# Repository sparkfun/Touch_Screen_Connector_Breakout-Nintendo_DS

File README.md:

SparkFun Touch Screen Connector Breakout - Nintendo DS
========================================

[*SparkFun Touch Screen Connector Breakout - Nintendo DS (BOB-09170)*](https://www.sparkfun.com/products/9170)

This a breakout board for the SMD connector for the Nintendo DS touch screen. 
4-pin right angle ZIF connector at 0.5 mm pitch broken out to 4 0.1 inch spaced headers.

Repository Contents
-------------------

* **/Hardware** - Eagle design files (.brd, .sch)
* **/Production** - Production panel files (.brd)

Documentation
--------------

* **[SparkFun Fritzing repo](https://github.com/sparkfun/Fritzing_Parts)** - Fritzing diagrams for SparkFun products.
* **[SparkFun 3D Model repo](https://github.com/sparkfun/3D_Models)** - 3D models of SparkFun products. 

License Information
-------------------
This product is _**open source**_! 

The **hardware** is released under [Creative Commons ShareAlike 4.0 International](https://creativecommons.org/licenses/by-sa/4.0/).

Please use, reuse, and modify these files as you see fit. Please maintain attribution to SparkFun Electronics and release anything derivative under the same license.

Distributed as-is; no warranty is given.

- Your friends at SparkFun.

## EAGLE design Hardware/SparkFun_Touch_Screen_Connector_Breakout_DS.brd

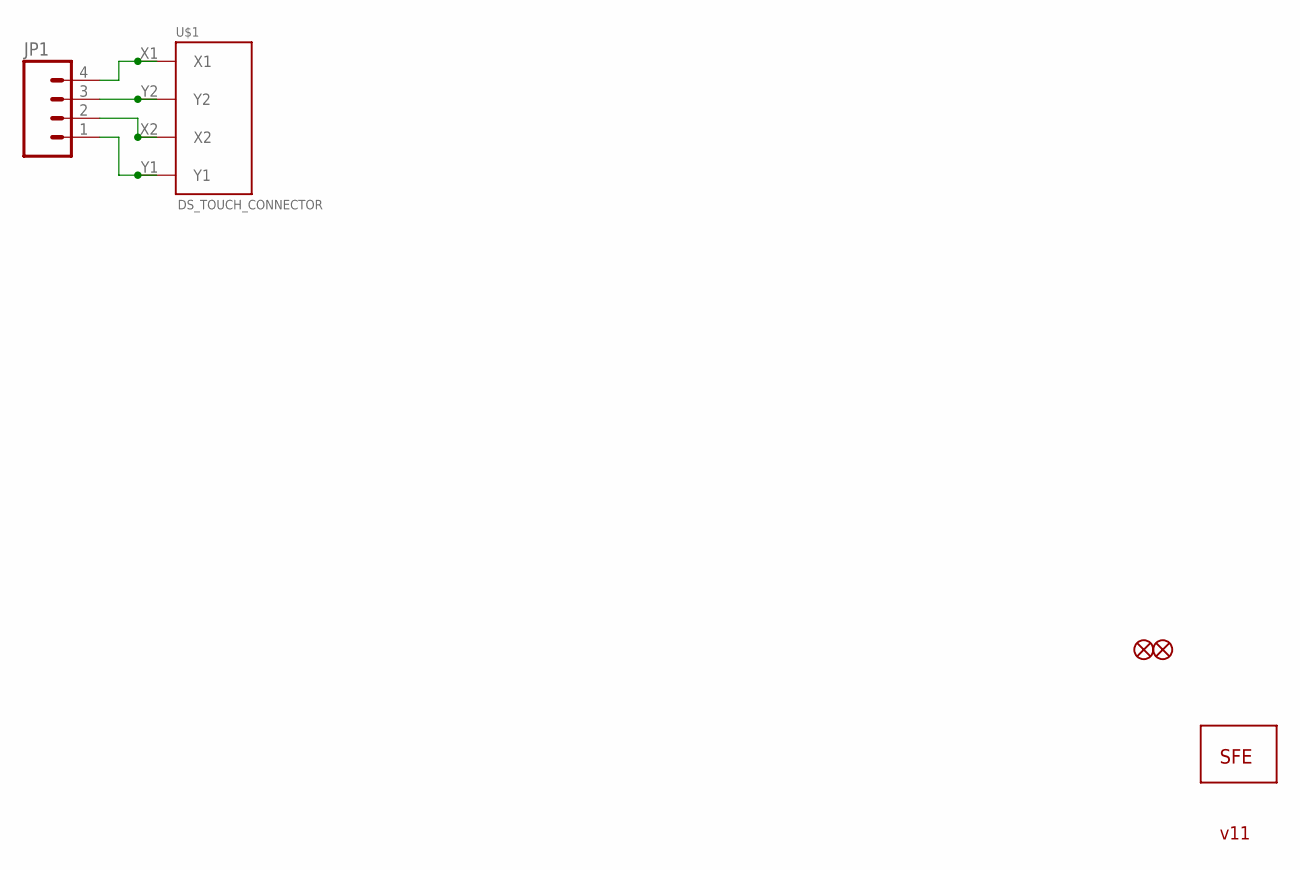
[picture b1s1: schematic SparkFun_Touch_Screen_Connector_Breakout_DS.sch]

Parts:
FID1, FID2: FIDUCIAL1X2; FIDUCIAL-1X2
JP1: M04PTH; 1X04
U$1: DS_TOUCH_CONNECTOR
U$2: LOGO-SFESK; SFE-LOGO-FLAME

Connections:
unnamed: JP1.4, U$1.X1
unnamed: JP1.3, U$1.Y2
unnamed: JP1.2, U$1.X2
unnamed: JP1.1, U$1.Y1

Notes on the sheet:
v11

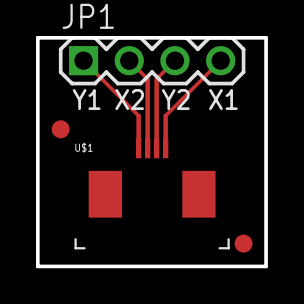
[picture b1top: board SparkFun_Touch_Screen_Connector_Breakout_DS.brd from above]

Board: 2 copper layers, 12.7 x 12.7 mm, 5 parts (1 on the bottom side), 4 nets.

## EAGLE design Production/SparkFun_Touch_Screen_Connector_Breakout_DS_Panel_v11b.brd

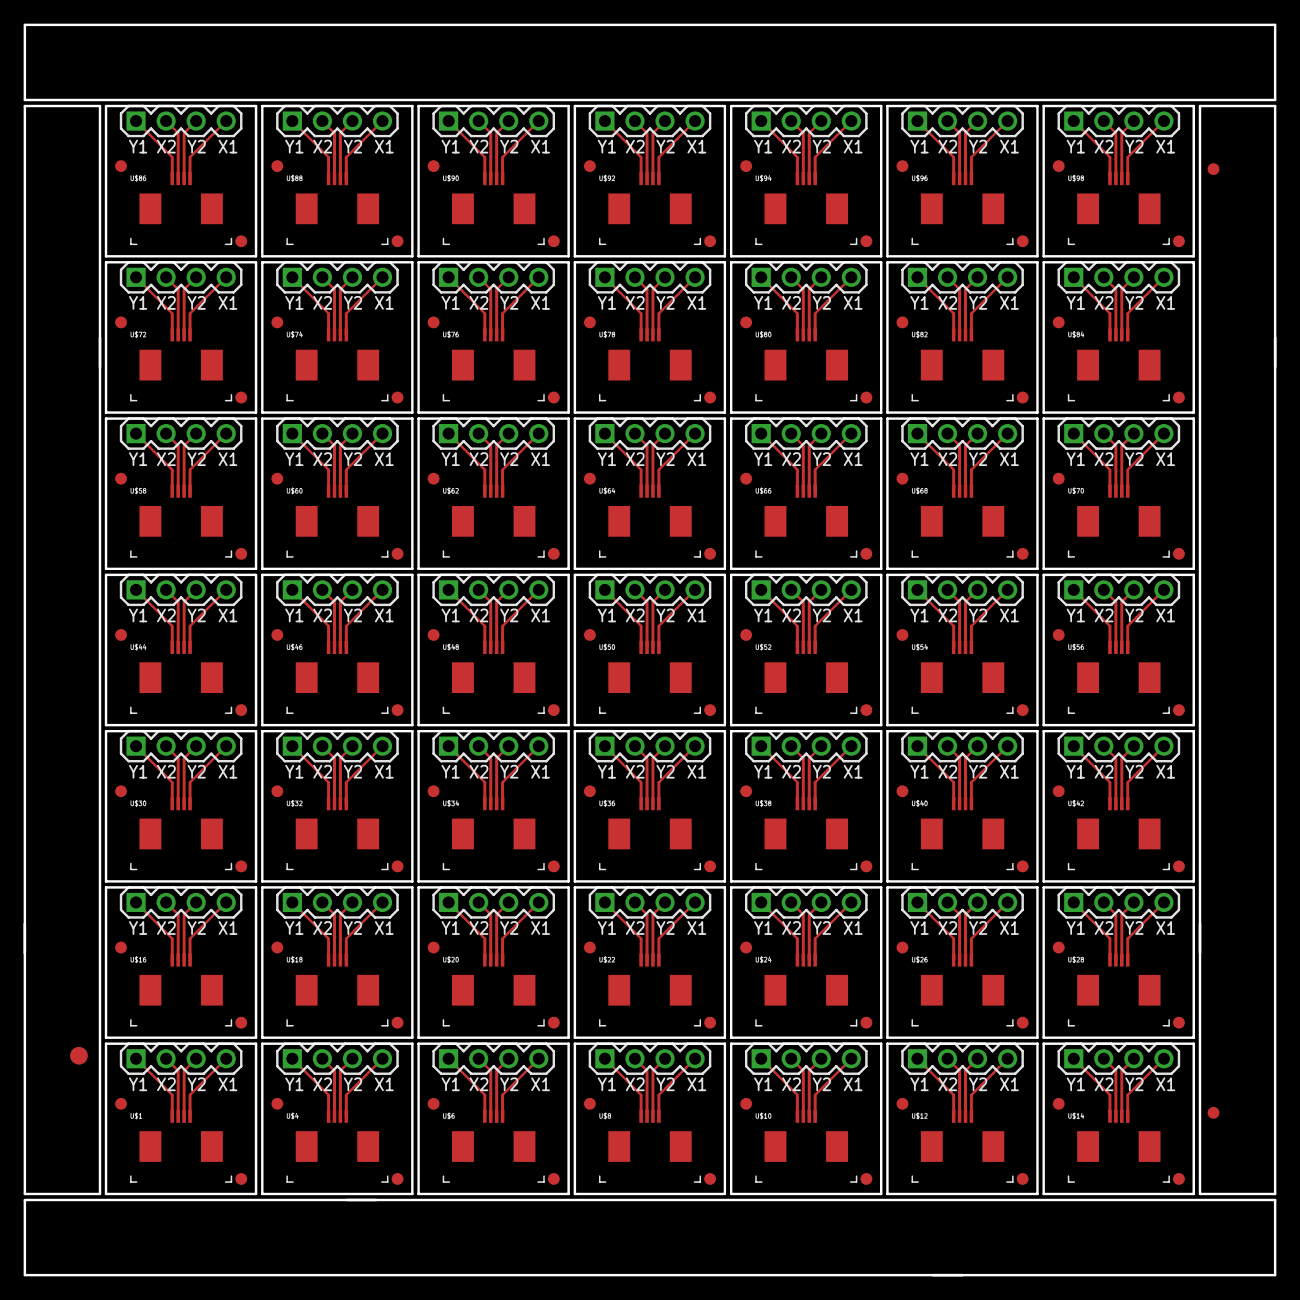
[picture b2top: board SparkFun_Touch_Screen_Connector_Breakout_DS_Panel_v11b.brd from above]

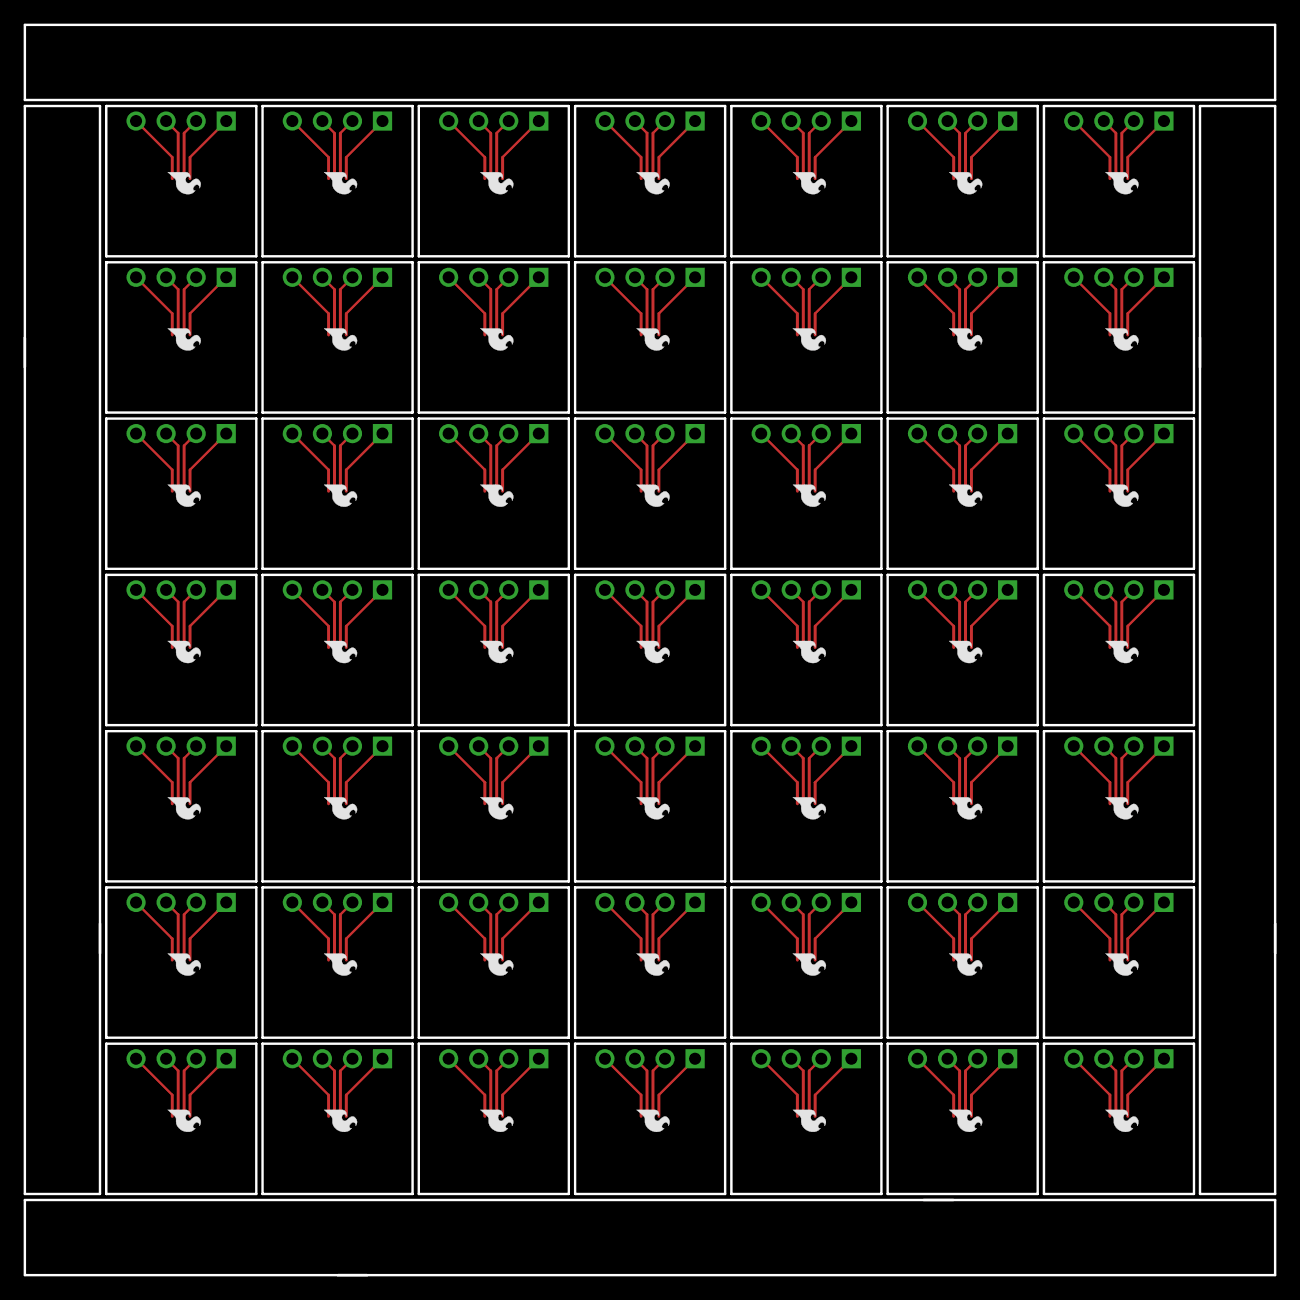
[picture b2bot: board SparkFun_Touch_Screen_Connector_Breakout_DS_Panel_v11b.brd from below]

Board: 2 copper layers, 105.7 x 105.7 mm, 248 parts (49 on the bottom side), 196 nets.

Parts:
E$1: FIDUCIAL-1.5X3
E$5, E$6: FIDUCIAL-1X2
FID1, FID2, FID3, FID4, FID5, FID6, FID7, FID8, FID9, FID10, FID11, FID12, FID13, FID14, FID15, FID16, FID17, FID18, FID19, FID20, FID21, FID22, FID23, FID24, FID25, FID26, FID27, FID28, FID29, FID30, FID31, FID32, FID33, FID34, FID35, FID36, FID37, FID38, FID39, FID40, FID41, FID42, FID43, FID44, FID45, FID46, FID47, FID48, FID49, FID50, FID51, FID52, FID53, FID54, FID55, FID56, FID57, FID58, FID59, FID60, FID61, FID62, FID63, FID64, FID65, FID66, FID67, FID68, FID69, FID70, FID71, FID72, FID73, FID74, FID75, FID76, FID77, FID78, FID79, FID80, FID81, FID82, FID83, FID84, FID85, FID86, FID87, FID88, FID89, FID90, FID91, FID92, FID93, FID94, FID95, FID96, FID97, FID98: FIDUCIAL1X2; FIDUCIAL-1X2
JP1, JP2, JP3, JP4, JP5, JP6, JP7, JP8, JP9, JP10, JP11, JP12, JP13, JP14, JP15, JP16, JP17, JP18, JP19, JP20, JP21, JP22, JP23, JP24, JP25, JP26, JP27, JP28, JP29, JP30, JP31, JP32, JP33, JP34, JP35, JP36, JP37, JP38, JP39, JP40, JP41, JP42, JP43, JP44, JP45, JP46, JP47, JP48, JP49: 1X04
U$1, U$4, U$6, U$8, U$10, U$12, U$14, U$16, U$18, U$20, U$22, U$24, U$26, U$28, U$30, U$32, U$34, U$36, U$38, U$40, U$42, U$44, U$46, U$48, U$50, U$52, U$54, U$56, U$58, U$60, U$62, U$64, U$66, U$68, U$70, U$72, U$74, U$76, U$78, U$80, U$82, U$84, U$86, U$88, U$90, U$92, U$94, U$96, U$98: DS_TOUCH_CONNECTOR
U$2, U$3, U$5, U$7, U$9, U$11, U$13, U$15, U$17, U$19, U$21, U$23, U$25, U$27, U$29, U$31, U$33, U$35, U$37, U$39, U$41, U$43, U$45, U$47, U$49, U$51, U$53, U$55, U$57, U$59, U$61, U$63, U$65, U$67, U$69, U$71, U$73, U$75, U$77, U$79, U$81, U$83, U$85, U$87, U$89, U$91, U$93, U$95, U$97: LOGO-SFESK; SFE-LOGO-FLAME

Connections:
unnamed: JP1.4, U$1.X1
unnamed: JP1.3, U$1.Y2
unnamed: JP1.2, U$1.X2
unnamed: JP1.1, U$1.Y1
unnamed: JP2.4, U$4.X1
unnamed: JP2.3, U$4.Y2
unnamed: JP2.2, U$4.X2
unnamed: JP2.1, U$4.Y1
unnamed: JP3.4, U$6.X1
unnamed: JP3.3, U$6.Y2
unnamed: JP3.2, U$6.X2
unnamed: JP3.1, U$6.Y1
unnamed: JP4.4, U$8.X1
unnamed: JP4.3, U$8.Y2
unnamed: JP4.2, U$8.X2
unnamed: JP4.1, U$8.Y1
unnamed: JP5.4, U$10.X1
unnamed: JP5.3, U$10.Y2
unnamed: JP5.2, U$10.X2
unnamed: JP5.1, U$10.Y1
unnamed: JP6.4, U$12.X1
unnamed: JP6.3, U$12.Y2
unnamed: JP6.2, U$12.X2
unnamed: JP6.1, U$12.Y1
unnamed: JP7.4, U$14.X1
unnamed: JP7.3, U$14.Y2
unnamed: JP7.2, U$14.X2
unnamed: JP7.1, U$14.Y1
unnamed: JP8.4, U$16.X1
unnamed: JP8.3, U$16.Y2
unnamed: JP8.2, U$16.X2
unnamed: JP8.1, U$16.Y1
unnamed: JP9.4, U$18.X1
unnamed: JP9.3, U$18.Y2
unnamed: JP9.2, U$18.X2
unnamed: JP9.1, U$18.Y1
unnamed: JP10.4, U$20.X1
unnamed: JP10.3, U$20.Y2
unnamed: JP10.2, U$20.X2
unnamed: JP10.1, U$20.Y1
unnamed: JP11.4, U$22.X1
unnamed: JP11.3, U$22.Y2
unnamed: JP11.2, U$22.X2
unnamed: JP11.1, U$22.Y1
unnamed: JP12.4, U$24.X1
unnamed: JP12.3, U$24.Y2
unnamed: JP12.2, U$24.X2
unnamed: JP12.1, U$24.Y1
unnamed: JP13.4, U$26.X1
unnamed: JP13.3, U$26.Y2
unnamed: JP13.2, U$26.X2
unnamed: JP13.1, U$26.Y1
unnamed: JP14.4, U$28.X1
unnamed: JP14.3, U$28.Y2
unnamed: JP14.2, U$28.X2
unnamed: JP14.1, U$28.Y1
unnamed: JP15.4, U$30.X1
unnamed: JP15.3, U$30.Y2
unnamed: JP15.2, U$30.X2
unnamed: JP15.1, U$30.Y1
unnamed: JP16.4, U$32.X1
unnamed: JP16.3, U$32.Y2
unnamed: JP16.2, U$32.X2
unnamed: JP16.1, U$32.Y1
unnamed: JP17.4, U$34.X1
unnamed: JP17.3, U$34.Y2
unnamed: JP17.2, U$34.X2
unnamed: JP17.1, U$34.Y1
unnamed: JP18.4, U$36.X1
unnamed: JP18.3, U$36.Y2
unnamed: JP18.2, U$36.X2
unnamed: JP18.1, U$36.Y1
unnamed: JP19.4, U$38.X1
unnamed: JP19.3, U$38.Y2
unnamed: JP19.2, U$38.X2
unnamed: JP19.1, U$38.Y1
unnamed: JP20.4, U$40.X1
unnamed: JP20.3, U$40.Y2
unnamed: JP20.2, U$40.X2
unnamed: JP20.1, U$40.Y1
unnamed: JP21.4, U$42.X1
unnamed: JP21.3, U$42.Y2
unnamed: JP21.2, U$42.X2
unnamed: JP21.1, U$42.Y1
unnamed: JP22.4, U$44.X1
unnamed: JP22.3, U$44.Y2
unnamed: JP22.2, U$44.X2
unnamed: JP22.1, U$44.Y1
unnamed: JP23.4, U$46.X1
unnamed: JP23.3, U$46.Y2
unnamed: JP23.2, U$46.X2
unnamed: JP23.1, U$46.Y1
unnamed: JP24.4, U$48.X1
unnamed: JP24.3, U$48.Y2
unnamed: JP24.2, U$48.X2
unnamed: JP24.1, U$48.Y1
unnamed: JP25.4, U$50.X1
unnamed: JP25.3, U$50.Y2
unnamed: JP25.2, U$50.X2
unnamed: JP25.1, U$50.Y1
unnamed: JP26.4, U$52.X1
unnamed: JP26.3, U$52.Y2
unnamed: JP26.2, U$52.X2
unnamed: JP26.1, U$52.Y1
unnamed: JP27.4, U$54.X1
unnamed: JP27.3, U$54.Y2
unnamed: JP27.2, U$54.X2
unnamed: JP27.1, U$54.Y1
unnamed: JP28.4, U$56.X1
unnamed: JP28.3, U$56.Y2
unnamed: JP28.2, U$56.X2
unnamed: JP28.1, U$56.Y1
unnamed: JP29.4, U$58.X1
unnamed: JP29.3, U$58.Y2
unnamed: JP29.2, U$58.X2
unnamed: JP29.1, U$58.Y1
unnamed: JP30.4, U$60.X1
unnamed: JP30.3, U$60.Y2
unnamed: JP30.2, U$60.X2
unnamed: JP30.1, U$60.Y1
unnamed: JP31.4, U$62.X1
unnamed: JP31.3, U$62.Y2
unnamed: JP31.2, U$62.X2
unnamed: JP31.1, U$62.Y1
unnamed: JP32.4, U$64.X1
unnamed: JP32.3, U$64.Y2
unnamed: JP32.2, U$64.X2
unnamed: JP32.1, U$64.Y1
unnamed: JP33.4, U$66.X1
unnamed: JP33.3, U$66.Y2
unnamed: JP33.2, U$66.X2
unnamed: JP33.1, U$66.Y1
unnamed: JP34.4, U$68.X1
unnamed: JP34.3, U$68.Y2
unnamed: JP34.2, U$68.X2
unnamed: JP34.1, U$68.Y1
unnamed: JP35.4, U$70.X1
unnamed: JP35.3, U$70.Y2
unnamed: JP35.2, U$70.X2
unnamed: JP35.1, U$70.Y1
unnamed: JP36.4, U$72.X1
unnamed: JP36.3, U$72.Y2
unnamed: JP36.2, U$72.X2
unnamed: JP36.1, U$72.Y1
unnamed: JP37.4, U$74.X1
unnamed: JP37.3, U$74.Y2
unnamed: JP37.2, U$74.X2
unnamed: JP37.1, U$74.Y1
unnamed: JP38.4, U$76.X1
unnamed: JP38.3, U$76.Y2
unnamed: JP38.2, U$76.X2
unnamed: JP38.1, U$76.Y1
unnamed: JP39.4, U$78.X1
unnamed: JP39.3, U$78.Y2
unnamed: JP39.2, U$78.X2
unnamed: JP39.1, U$78.Y1
unnamed: JP40.4, U$80.X1
unnamed: JP40.3, U$80.Y2
unnamed: JP40.2, U$80.X2
unnamed: JP40.1, U$80.Y1
unnamed: JP41.4, U$82.X1
unnamed: JP41.3, U$82.Y2
unnamed: JP41.2, U$82.X2
unnamed: JP41.1, U$82.Y1
unnamed: JP42.4, U$84.X1
unnamed: JP42.3, U$84.Y2
unnamed: JP42.2, U$84.X2
unnamed: JP42.1, U$84.Y1
unnamed: JP43.4, U$86.X1
unnamed: JP43.3, U$86.Y2
unnamed: JP43.2, U$86.X2
unnamed: JP43.1, U$86.Y1
unnamed: JP44.4, U$88.X1
unnamed: JP44.3, U$88.Y2
unnamed: JP44.2, U$88.X2
unnamed: JP44.1, U$88.Y1
unnamed: JP45.4, U$90.X1
unnamed: JP45.3, U$90.Y2
unnamed: JP45.2, U$90.X2
unnamed: JP45.1, U$90.Y1
unnamed: JP46.4, U$92.X1
unnamed: JP46.3, U$92.Y2
unnamed: JP46.2, U$92.X2
unnamed: JP46.1, U$92.Y1
unnamed: JP47.4, U$94.X1
unnamed: JP47.3, U$94.Y2
unnamed: JP47.2, U$94.X2
unnamed: JP47.1, U$94.Y1
unnamed: JP48.4, U$96.X1
unnamed: JP48.3, U$96.Y2
unnamed: JP48.2, U$96.X2
unnamed: JP48.1, U$96.Y1
unnamed: JP49.4, U$98.X1
unnamed: JP49.3, U$98.Y2
unnamed: JP49.2, U$98.X2
unnamed: JP49.1, U$98.Y1

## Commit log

2015-05-06 Adding hardware, readme
2015-12-23 added board fiducials
2015-12-23 created panel v11b

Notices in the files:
parts and their libraries:
SparkFun-Aesthetics: Licensing: Creative Commons ShareAlike 4.0 International - https://creativecommons.org/licenses/by-sa/4.0
